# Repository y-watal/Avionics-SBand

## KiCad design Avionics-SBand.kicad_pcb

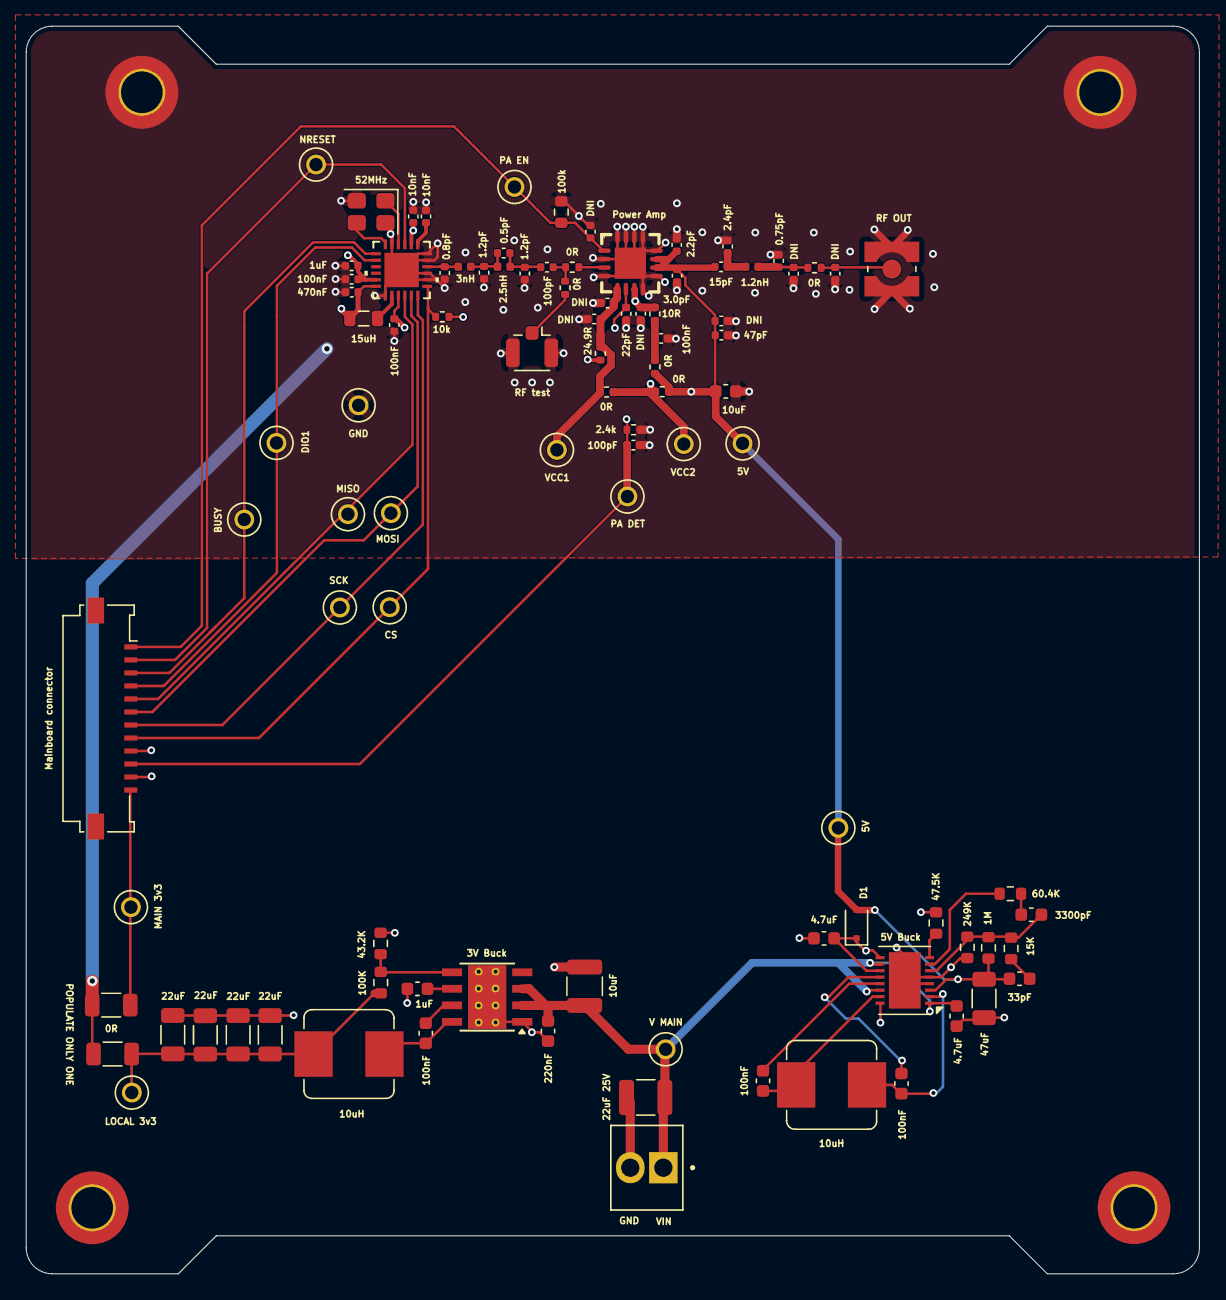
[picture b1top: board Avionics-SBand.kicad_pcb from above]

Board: 4 copper layers, 90.2 x 95.9 mm, 101 parts (0 on the bottom side), 46 nets.

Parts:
C1, C2, C35: 100nF; C_0402_1005Metric
C3, C5: 10nF; C_0402_1005Metric
C4: 470nF; C_0402_1005Metric
C6: 22uF 25V; C_1210_3225Metric
C7: 10uF; C_1210_3225Metric
C8: 220nF; C_0603_1608Metric
C9: 1uF; C_0603_1608Metric
C10, C24, C25: 100nF; C_0603_1608Metric
C11, C12, C13, C14: 22uF; C_1206_3216Metric
C15: 0.8pF; C_0402_1005Metric
C16, C17: 1.2pF; C_0402_1005Metric
C18, C32: 100pF; C_0402_1005Metric
C19: 0.5pF; C_0402_1005Metric
C20: 1uF; C_0402_1005Metric
C21, C23: 4.7uF; C_0603_1608Metric
C26: 3300pF; C_0603_1608Metric
C27: 33pF; C_0603_1608Metric
C28: 47uF; C_1206_3216Metric
C30, C33, C34, C36, C39, C45, C46: DNI; C_0402_1005Metric
C31: 22pF; C_0402_1005Metric
C40: 47pF; C_0402_1005Metric
C41: 2.2pF; C_0402_1005Metric
C47: 3.0pF; C_0402_1005Metric
C48: 10uF; C_0603_1608Metric
C49: 15pF; C_0402_1005Metric
C50: 2.4pF; C_0402_1005Metric
C51: 0.75pF; C_0402_1005Metric
D1: PMEG2010EJ; D_SOD-323F
H1, H2, H3, H4: MountingHole_Pad; MountingHole_3.2mm_M3_DIN965_Pad_TopBottom
J1: VIN; TE_282834-2
J2: Mainboard connector; Molex_200528-0120_1x12-1MP_P1.00mm_Horizontal
J3: RF test; U.FL_Hirose_U.FL-R-SMT-1_Vertical
J5: RF OUT; WR-MMCX_Wuerth_66012102111404_Vertical
L1: 15uH; L_0805_2012Metric
L2, L5: 10uH; L_Bourns_SRP7028A_7.3x6.6mm
L3: 3nH; L_0402_1005Metric
L4: 2.5nH; L_0402_1005Metric
L6: 1.2nH; L_0402_1005Metric
R1, R2: 0R; R_1206_3216Metric
R3: 100K; R_0603_1608Metric
R4: 43.2K; R_0603_1608Metric
R5, R6, R22, R25, R26, R27: 0R; R_0402_1005Metric
R7: 10k; R_0402_1005Metric
R8: 47.5K; R_0603_1608Metric
R9: 1M; R_0603_1608Metric
R10: 60.4K; R_0603_1608Metric
R11: 249K; R_0603_1608Metric
R12: 15K; R_0603_1608Metric
R16: 100k; R_0603_1608Metric
R17: 2.4k; R_0402_1005Metric
R21: 24.9R; R_0402_1005Metric
R23: 10R; R_0402_1005Metric
TP1: V MAIN; KEYSTONE_5001
TP2: LOCAL 3v3; KEYSTONE_5001
TP3: NRESET; KEYSTONE_5001
TP4: BUSY; KEYSTONE_5001
TP5: DIO1; KEYSTONE_5001
TP6: CS; KEYSTONE_5001
TP7: SCK; KEYSTONE_5001
TP8: MOSI; KEYSTONE_5001
TP9: MISO; KEYSTONE_5001
TP10, TP16: 5V; KEYSTONE_5001
TP11: PA EN; KEYSTONE_5001
TP13: PA DET; KEYSTONE_5001
TP14: VCC1; KEYSTONE_5001
TP15: VCC2; KEYSTONE_5001
TP17: MAIN 3v3; KEYSTONE_5001
TP18: GND; KEYSTONE_5001
U1: TXVR; QFN24_4X4_SEM
U2: 3V Buck; Texas_HSOP-8-1EP_3.9x4.9mm_P1.27mm_ThermalVias
U3: Power Amp; VQFN-16_L4_0-W4_0-P0_65-BL-EP2_4_SKY65900-11_C1870175
U4: 5V Buck; DFN-16-1EP_4x5mm_P0.5mm_EP2.44x4.34mm
Y1: 52MHz; Crystal_SMD_3225-4Pin_3.2x2.5mm

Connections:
5V: C27.1, C28.1, C39.1, C40.1, C41.1, C47.1, C48.1, C49.1, D1.2 (A), R9.2, R21.1, R22.1, R27.2, TP10.TP, TP16.TP, U3.10, U3.11, U4.3
+3V3: C1.2, C2.2, C20.1, R1.2, R2.2, R7.1, U1.11 (VBAT_IO), U1.15 (VBAT)
/Connectors/VCC_5V: C23.1, D1.1 (K), U4.9, U4.11, U4.16
/PA_to_Antenna/PA_DET: C31.1, C32.1, J2.10, R17.1, TP13.TP, U3.6
/PA_to_Antenna/PA_EN: C30.1, J2.1, R16.1, TP11.TP, U3.1
/PA_to_Antenna/PA_RF_IN: R6.1, U3.3
/PA_to_Antenna/VCC1: C33.1, C34.1, R21.2, R26.1, TP14.TP, U3.5
/PA_to_Antenna/VCC2: C36.1, R23.2, R26.2, R27.1, TP15.TP, U3.7
/SX1280/BUSY: J2.3, TP4.TP, U1.7 (BUSY)
/SX1280/DIO1: J2.4, TP5.TP, U1.8 (DIO1)
/SX1280/NRESET: J2.2, TP3.TP, U1.3 (NRESET)
/SX1280/RFIO: C15.2, L3.1, U1.22 (RFIO)
/SX1280/SPI_CS: J2.8, R7.2, TP6.TP, U1.19 (NSS_CTS)
/SX1280/SPI_MISO: J2.5, TP9.TP, U1.16 (MISO_TX)
/SX1280/SPI_MOSI: J2.6, TP8.TP, U1.17 (MOSI_RX)
/SX1280/SPI_SCK: J2.7, TP7.TP, U1.18 (SCK_RTSN)
/SX1280/XTA: U1.4 (XTA), Y1.1
/SX1280/XTB: U1.6 (XTB), Y1.3
GND: C1.1, C2.1, C3.2, C4.2, C5.2, C6.2, C7.1, C8.1, C9.1, C11.1, C12.1, C13.1, C14.1, C15.1, C16.1, C17.1, C20.2, C21.1, C23.2, C28.2, C30.2, C31.2, C32.2, C33.2, C34.2, C35.2, C36.2, C39.2, C40.2, C41.2, C45.2, C46.2, C47.2, C48.2, C50.2, C51.2, H1.1 (1_1), H2.1 (1_1), H3.1 (1_1), H4.1 (1_1), J1.2, J2.9, J2.11, J3.2 (Ext), J5.2 (Ext), R4.2, R8.1, R11.1, R16.2, R17.2, TP18.TP, U1.5 (GND), U1.13 (GND), U1.20 (GND), U1.21 (GND), U1.23 (GND), U1.24 (GND), U1.25 (GND), U2.1 (GND), U2.9 (GND), U3.2, U3.4, U3.8, U3.9, U3.12, U3.13, U3.14, U3.15, U3.16, U3.17, U4.4, U4.5, U4.17, Y1.2 (G), Y1.4 (G)
LOCAL_3V3: C11.2, C12.2, C13.2, C14.2, L2.2, R2.1, R3.1, TP2.TP
MAIN_3V3: J2.12, R1.1, TP17.TP
unnamed: C16.2, C19.1, L3.2, L4.1
unnamed: C17.2, C18.1, C19.2, L4.2
unnamed: C18.2, R5.2, R6.2
unnamed: C24.1, U4.13
unnamed: C24.2, L5.1, U4.15
unnamed: C25.1, L5.2, U4.2
unnamed: C25.2, U4.12
unnamed: C26.1, R10.2
unnamed: C26.2, R9.1, R11.2, R12.1, U4.6
unnamed: C27.2, R12.2
unnamed: C35.1, R22.2, R23.1
unnamed: C45.1, C51.1, L6.2, R25.1
unnamed: C49.2, C50.1, L6.1
unnamed: J3.1 (In), R5.1
unnamed: C46.1, J5.1 (In), R25.2
unnamed: R8.2, U4.8
unnamed: R10.1, U4.7
unnamed: C3.1, C4.1, L1.1, U1.2 (VDD_IN), U1.12 (DCC_FB)
unnamed: L1.2, U1.14 (DCC_SW)
unnamed: C5.1, U1.1 (VR_PA)
unnamed: C10.1, U2.7 (BOOT)
unnamed: R3.2, R4.1, U2.5 (FB)
unnamed: C10.2, L2.1, U2.8 (SW)
unnamed: C9.2, U2.6 (VCC)
V_MAIN: C6.1, C7.2, C8.2, C21.2, J1.1, TP1.TP, U2.2 (VIN), U2.3 (EN), U4.1, U4.10, U4.14
